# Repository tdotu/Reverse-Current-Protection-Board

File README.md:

# Reverse-Current-Protection-Board
A Reverse Current Protection Board that allows the safe paralell usage of two Battery packs with different capacities.

## What it does

I developed this board because I wanted to use two 10S5P battery packs with different cells in paralell. Each of the packs has it's own BMS with seperate charge and discharge negative pole. This board takes care that the two packs do not charge and discharge each ohter. It also allows the enableing and disableing of the charing and discharging of each pack.

## Electrical limits
This board is designed for a maximal load of 55A on the discharge output when it is
fabricated with 70µm (2oz) of copper. It can be used up until a 14s (48V) battery packs.

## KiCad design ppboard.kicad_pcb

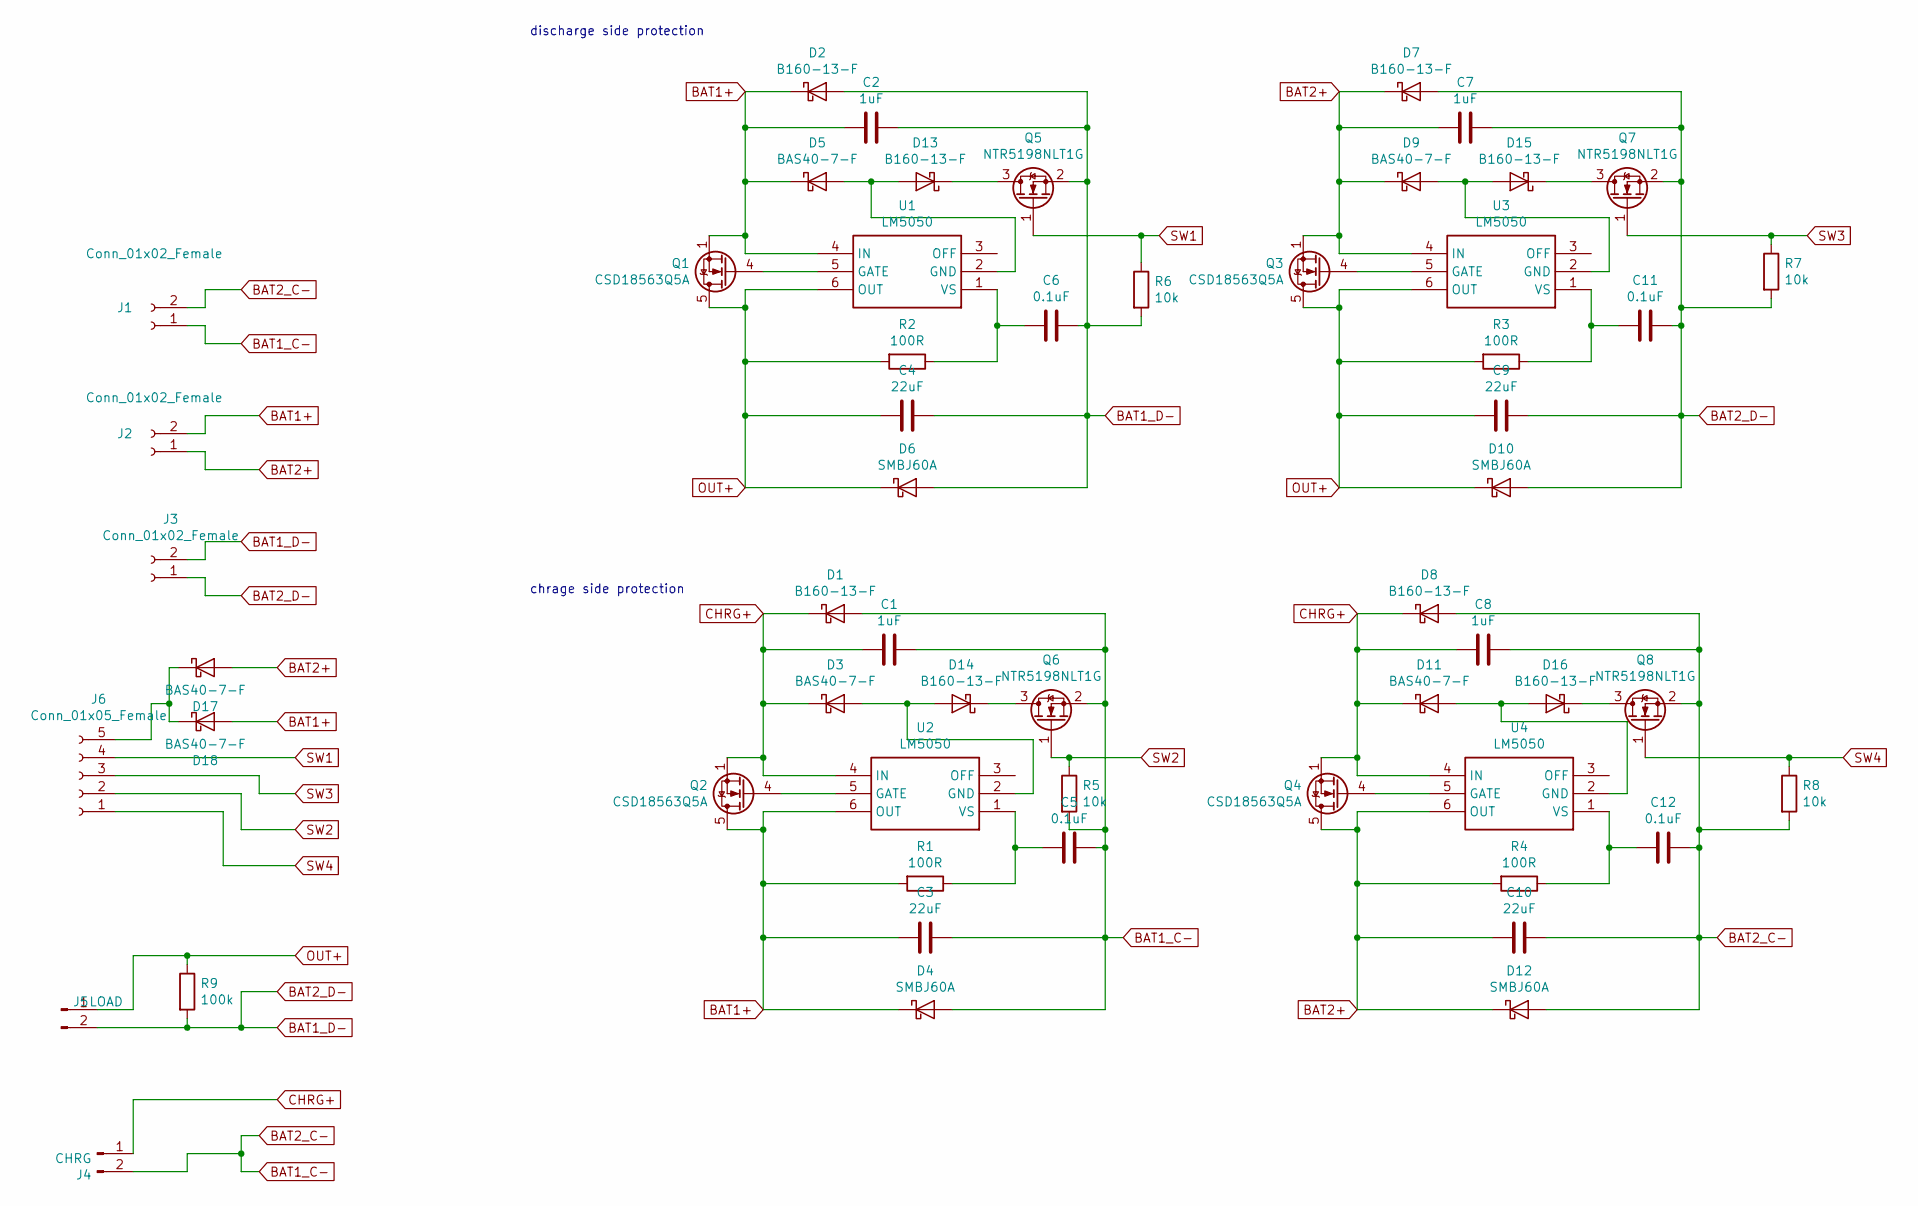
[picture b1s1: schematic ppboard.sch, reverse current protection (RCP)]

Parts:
C1, C7, C8: 1uF; C_0805_2012Metric; voltage 75v
C2: 1uF; C_0805_2012Metric; voltage 75V
C3, C4, C9, C10: 22uF; CP_Elec_6.3x5.2
C5, C11: 0.1uF; C_0805_2012Metric; voltage 100V
C6, C12: 0.1uF; C_0805_2012Metric; Voltage 100V
D1, D7, D8, D13, D14, D15, D16: B160-13-F; D_SMA
D2: B160-13-F; D_SMA; voltage 60V
D3, D5, D9, D11, D17, D18: BAS40-7-F; D_SOT-23_ANK
D4, D6, D10, D12: SMBJ60A; D_SMA
J1, J2, J3: Conn_01x02_Female; XT60PW
J4: CHRG; XT60PW
J5: LOAD; XT60PW
J6: Conn_01x05_Female; JST_PH_S5B-PH-K_1x05_P2.00mm_Horizontal
Q1, Q2, Q3, Q4: CSD18563Q5A; TDSON-8-1
Q5, Q6, Q7, Q8: NTR5198NLT1G; SOT-23
R1, R2, R3, R4: 100R; R_0603_1608Metric
R5, R6, R7, R8: 10k; R_0603_1608Metric
R9: 100k; R_0805_2012Metric
U1, U2, U3, U4: LM5050; Texas_R-PDSO-G6

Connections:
BAT1+: C2.2, C3.1, D2.1 (K), D4.1 (K), D5.1 (K), D18.2 (A), J2.2, Q1.1 (S), Q1.2 (S), Q1.3 (S), Q2.5 (D), R1.2, U1.4 (IN), U2.6 (OUT)
BAT1_C-: C1.1, C3.2, C5.2, C8.1, C10.2, C12.2, D1.2 (A), D4.2 (A), D8.2 (A), D12.2 (A), J1.1, J1.2, J4.2, Q6.2 (S), Q8.2 (S), R5.2, R8.2
BAT1_D-: C2.1, C4.2, C6.2, C7.1, C9.2, C11.2, D2.2 (A), D6.2 (A), D7.2 (A), D10.2 (A), J3.1, J3.2, J5.2, Q5.2 (S), Q7.2 (S), R6.2, R7.2, R9.2
BAT2+: C7.2, C10.1, D7.1 (K), D9.1 (K), D12.1 (K), D17.2 (A), J2.1, Q3.1 (S), Q3.2 (S), Q3.3 (S), Q4.5 (D), R4.2, U3.4 (IN), U4.6 (OUT)
CHRG+: C1.2, C8.2, D1.1 (K), D3.1 (K), D8.1 (K), D11.1 (K), J4.1, Q2.1 (S), Q2.2 (S), Q2.3 (S), Q4.1 (S), Q4.2 (S), Q4.3 (S), U2.4 (IN), U4.4 (IN)
unnamed: C5.1, R1.1, U2.1 (VS)
unnamed: C6.1, R2.1, U1.1 (VS)
unnamed: C11.1, R3.1, U3.1 (VS)
unnamed: C12.1, R4.1, U4.1 (VS)
unnamed: D11.2 (A), D16.2 (A), U4.2 (GND)
unnamed: D13.1 (K), Q5.3 (D)
unnamed: D5.2 (A), D13.2 (A), U1.2 (GND)
unnamed: D14.1 (K), Q6.3 (D)
unnamed: D3.2 (A), D14.2 (A), U2.2 (GND)
unnamed: D15.1 (K), Q7.3 (D)
unnamed: D9.2 (A), D15.2 (A), U3.2 (GND)
unnamed: D16.1 (K), Q8.3 (D)
unnamed: D17.1 (K), D18.1 (K), J6.5
unnamed: Q1.4 (G), U1.5 (GATE)
unnamed: Q2.4 (G), U2.5 (GATE)
unnamed: Q3.4 (G), U3.5 (GATE)
unnamed: Q4.4 (G), U4.5 (GATE)
OUT+: C4.1, C9.1, D6.1 (K), D10.1 (K), J5.1, Q1.5 (D), Q3.5 (D), R2.2, R3.2, R9.1, U1.6 (OUT), U3.6 (OUT)
SW1: J6.4, Q5.1 (G), R6.1
SW2: J6.2, Q6.1 (G), R5.1
SW3: J6.3, Q7.1 (G), R7.1
SW4: J6.1, Q8.1 (G), R8.1

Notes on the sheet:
chrage side protection
discharge side protection

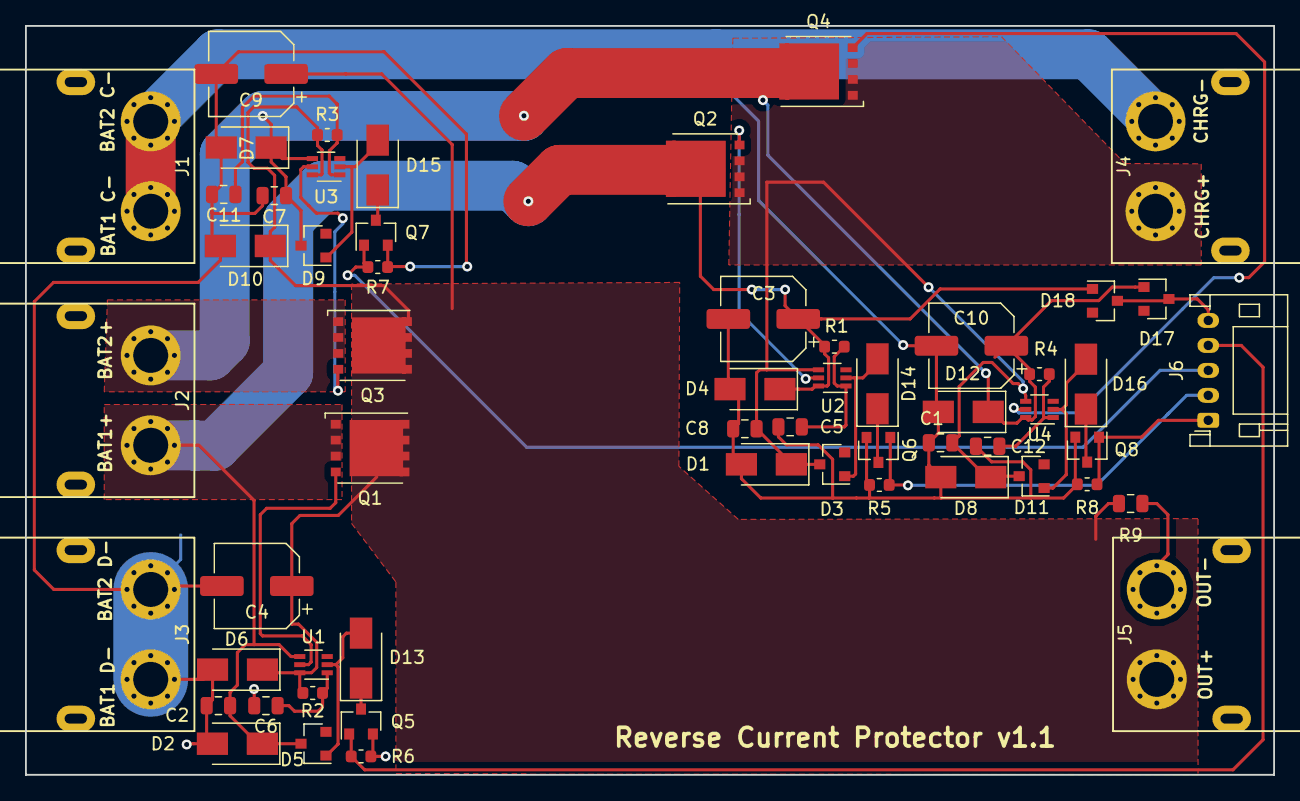
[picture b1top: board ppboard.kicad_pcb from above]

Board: 2 copper layers, 100.0 x 60.0 mm, 57 parts (0 on the bottom side), 27 nets.

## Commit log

2019-06-15 just pushed all the files. Will clean up later
2019-06-15 changed description
